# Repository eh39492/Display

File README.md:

# Display
This is week 4 of half life.
my project includes a 7-segment display, a microcontroller, and a button. upon a single button press, it will pick a random number from 0- 9 and display it. This can be used for many fun games.

ESP32-C3,1,Seeed,$4.99,$4.99,https://www.seeedstudio.com/Seeed-XIAO-ESP32C3-p-5431.html

Cherry MX,1,Aliexpress,$1.09,$1.09,https://www.aliexpress.us/item/3256808812099705.html?spm=a2g0o.cart.0.0.484c38daTrZ5Dy&mp=1&pdp_npi=6%40dis%21USD%21USD+17.73%21USD+5.36%21%21USD+5.36%21%21%21%4021032c8d17935673388878701e0f99%2112000047513088835%21ct%21US%21-1%21%211%210%21&_gl=1*1ev0qyb*_gcl_aw*R0NMLjE3OTM0NzA0OTAuQ2owS0NRanc4b2ZXQmhDSEFSSXNBTkJqNEx1UWh1UTBpQkk4TkpkYXgzZ0tWdEJZUWUySFJWc2hVRXJhNGRfdGdKOTZpQzFMcVI3Z1dYSWFBcy1CRUFMd193Y0I.*_gcl_dc*R0NMLjE3OTM0NzA0OTAuQ2owS0NRanc4b2ZXQmhDSEFSSXNBTkJqNEx1UWh1UTBpQkk4TkpkYXgzZ0tWdEJZUWUySFJWc2hVRXJhNGRfdGdKOTZpQzFMcVI3Z1dYSWFBcy1CRUFMd193Y0I.*_gcl_au*MTQyNjI2MzAyMy4xNzkxNzQ2MDUy*_ga*MTI3NzA3NzMxMi4xNzkyOTYyMjEz*_ga_VED1YSGNC7*czE3OTM1NjY4OTckbzYkZzEkdDE3OTM1NjczNTUkajMzJGwwJGgw&gatewayAdapt=glo2usa

220ohm Resitors,1,Aliexpress,$2.57,$2.57,https://aliexpress.com/item/3256802202400215.html?spm=a2g0o.cart.0.0.69c338darV6IDP&mp=1&pdp_npi=6%40dis%21USD%21USD%202.57%21USD%201.09%21%21USD%201.09%21%21%21%4021032c8d17935673604301672e0f99%2112000020473148746%21ct%21US%21-1%21%211%210%21&_gl=1*1uiursq*_gcl_aw*R0NMLjE3OTM0NzA0OTAuQ2owS0NRanc4b2ZXQmhDSEFSSXNBTkJqNEx1UWh1UTBpQkk4TkpkYXgzZ0tWdEJZUWUySFJWc2hVRXJhNGRfdGdKOTZpQzFMcVI3Z1dYSWFBcy1CRUFMd193Y0I.*_gcl_dc*R0NMLjE3OTM0NzA0OTAuQ2owS0NRanc4b2ZXQmhDSEFSSXNBTkJqNEx1UWh1UTBpQkk4TkpkYXgzZ0tWdEJZUWUySFJWc2hVRXJhNGRfdGdKOTZpQzFMcVI3Z1dYSWFBcy1CRUFMd193Y0I.*_gcl_au*MTQyNjI2MzAyMy4xNzkxNzQ2MDUy*_ga*MTI3NzA3NzMxMi4xNzkyOTYyMjEz*_ga_VED1YSGNC7*czE3OTM1NjY4OTckbzYkZzEkdDE3OTM1Njc0MjckajYwJGwwJGgw

PCB,1,JLCpcb,$4.00,$4.00,https://jlcpcb.com/

7 segment display,1,Amazon,$8.59,$8.59,https://www.amazon.com/gp/product/B0C5MQQ7DM/ref=ox_sc_act_title_1?smid=AF9CPILHGHOMP&psc=1

Estimated total shipping,1,,,$9.00,

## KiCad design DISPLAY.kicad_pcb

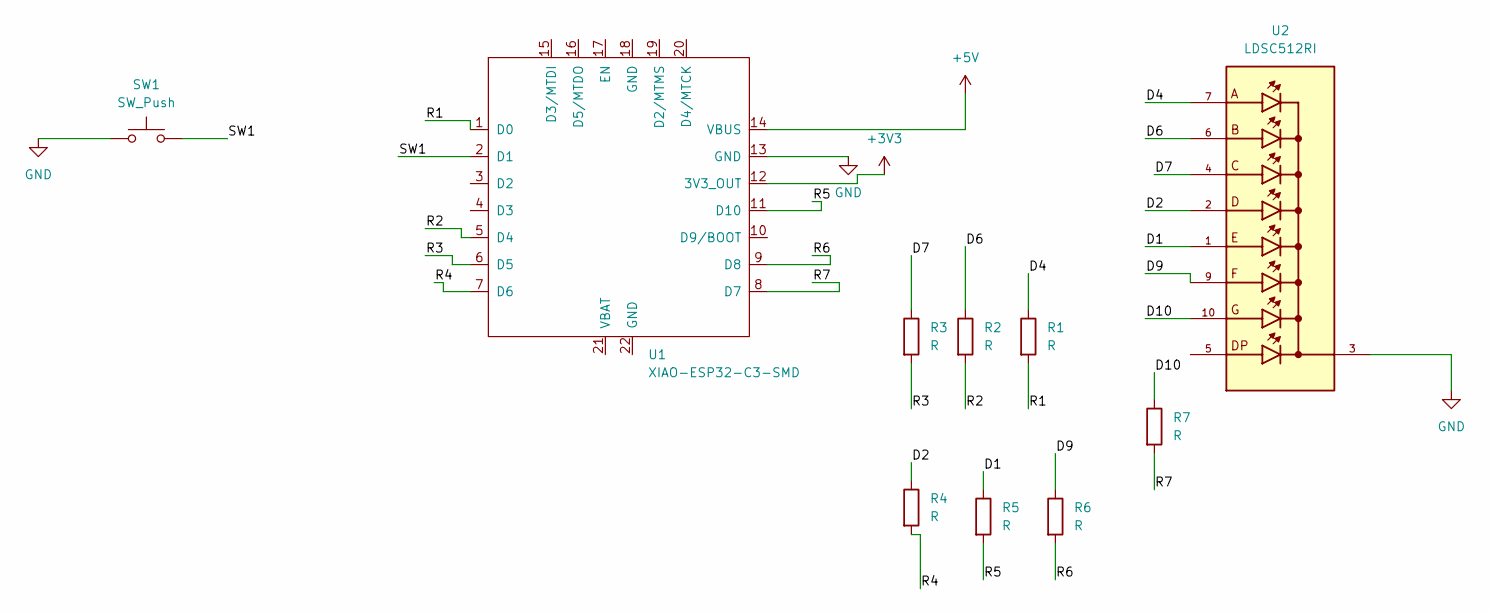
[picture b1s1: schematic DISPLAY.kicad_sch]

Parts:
R1: R; DIP-8_W7.62mm
R2, R3, R4, R5, R6, R7: R
SW1: SW_Push; SW_NKK_GW12LJP
U1: XIAO-ESP32-C3-SMD
U2: LDSC512RI; LED_LDSC512RI; PARTREV A

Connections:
+3V3: U1.12 (3V3_OUT)
+5V: U1.14 (VBUS)
/<NO NET>: R3.1, U2.4
/D1: R5.1, U2.1
/D2: R4.1, U2.2
/D4: R1.1, U2.7
/D6: R2.1, U2.6
/D9: R6.1, U2.9
/D10: R7.1, U2.10
/R1: R1.2, U1.1 (D0)
/R2: R2.2, U1.5 (D4)
/R3: R3.2, U1.6 (D5)
/R4: R4.2, U1.7 (D6)
/R5: R5.2, U1.11 (D10)
/R6: R6.2, U1.9 (D8)
/R7: R7.2, U1.8 (D7)
/SW1: SW1.2, U1.2 (D1)
GND: SW1.1, U1.13 (GND), U2.3, U2.8

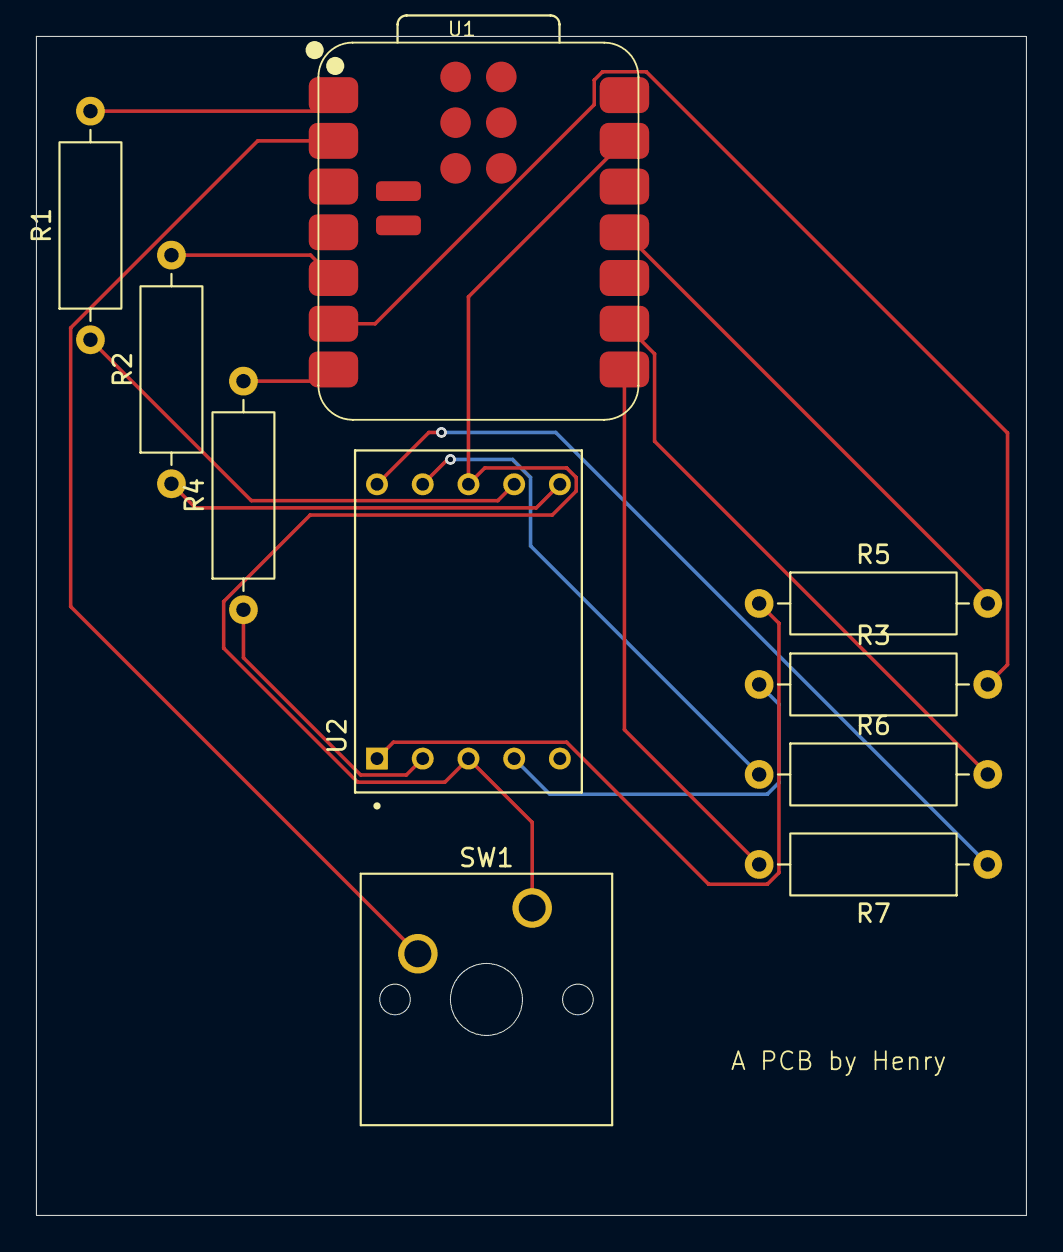
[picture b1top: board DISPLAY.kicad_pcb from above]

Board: 2 copper layers, 55.0 x 65.5 mm, 10 parts (0 on the bottom side), 16 nets.
